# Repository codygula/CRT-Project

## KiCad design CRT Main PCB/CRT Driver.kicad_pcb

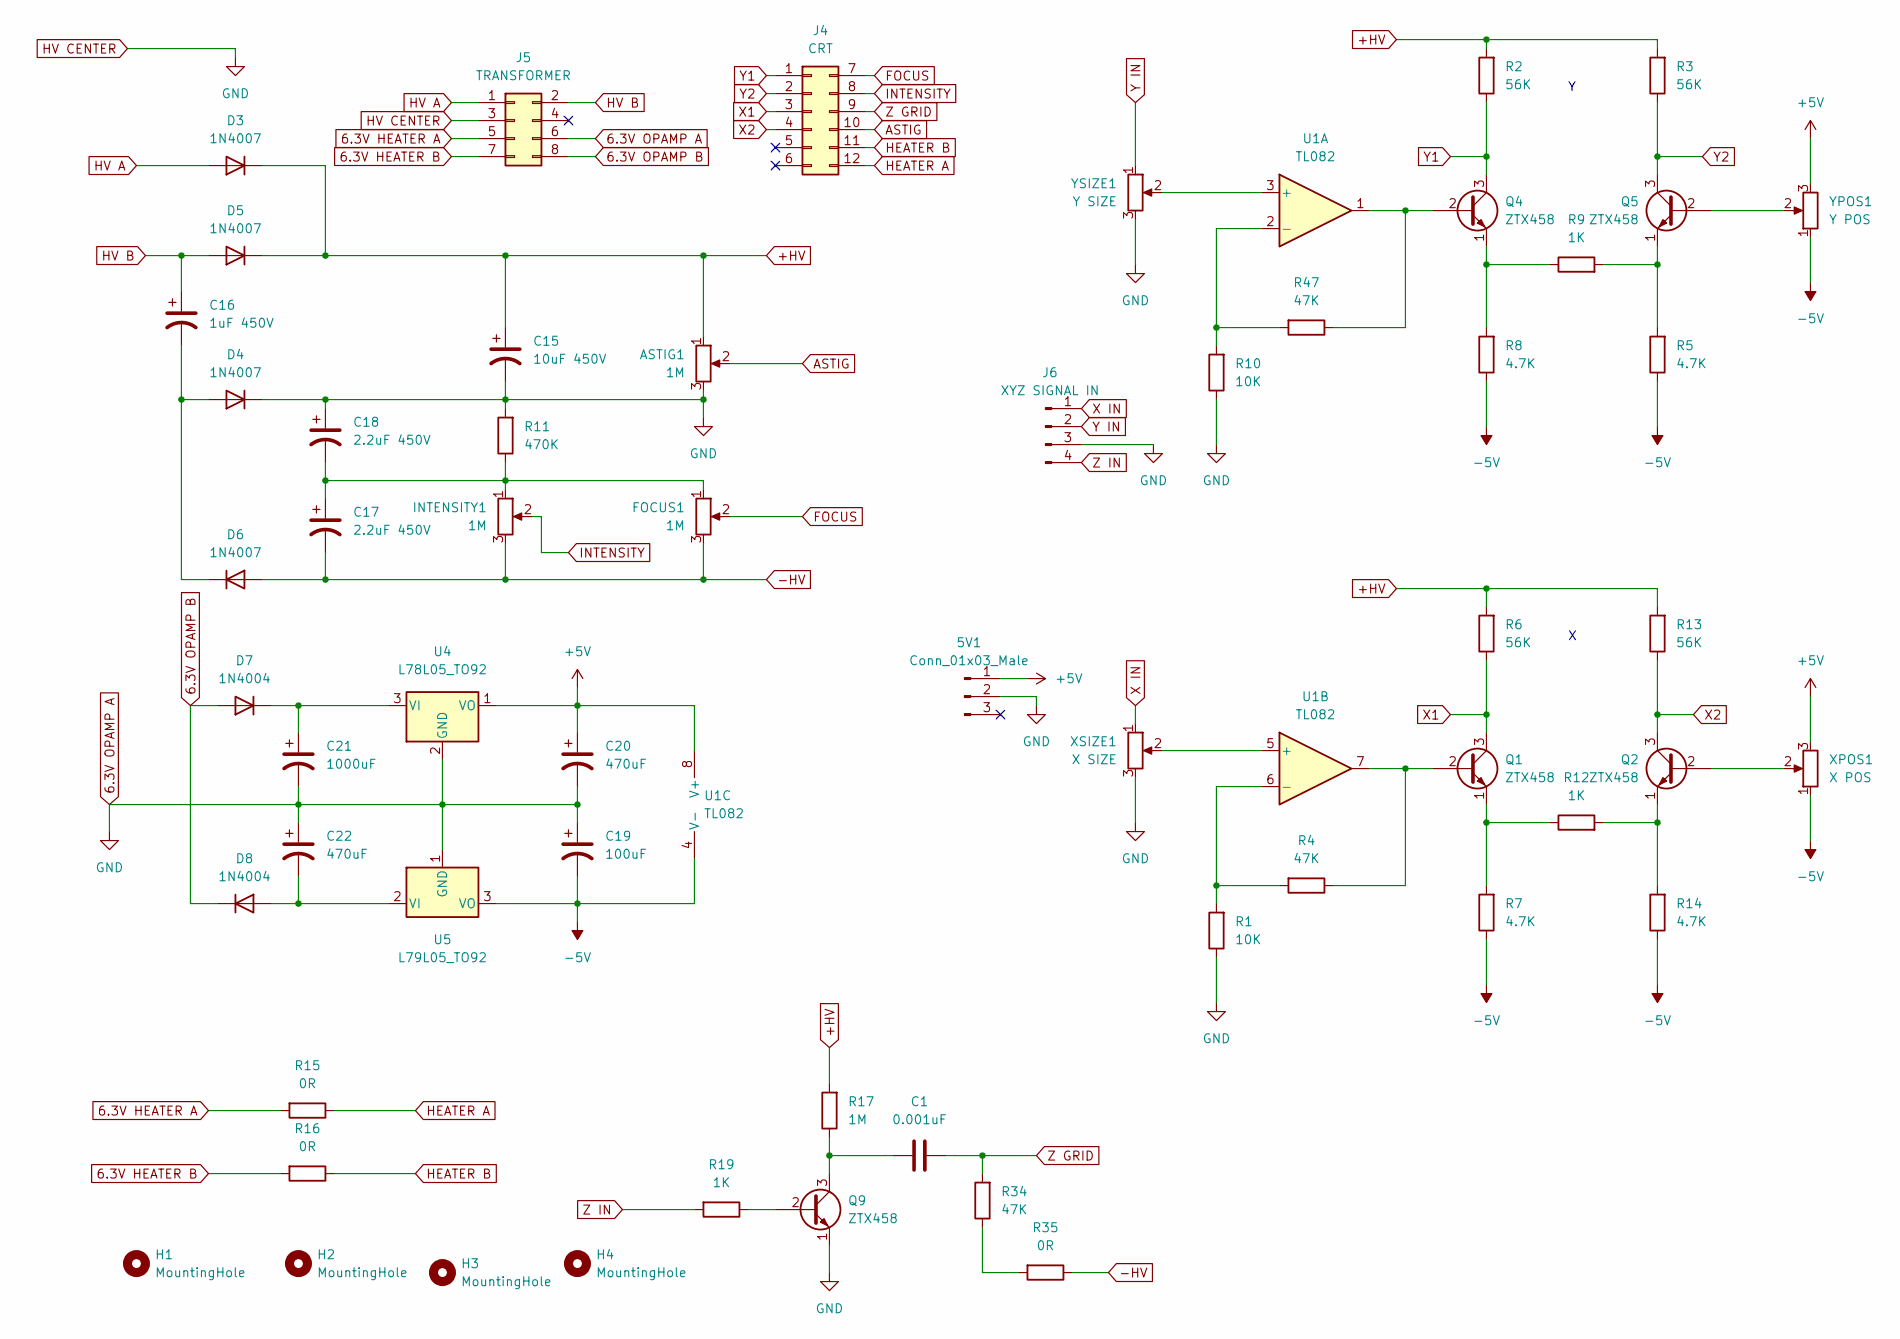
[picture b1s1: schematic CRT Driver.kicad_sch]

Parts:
5V1: Conn_01x03_Male; PinHeader_1x03_P2.54mm_Vertical
ASTIG1: 1M; Trimmer
C1: 0.001uF; C_Disc_D7.5mm_W5.0mm_P5.00mm
C15: 10uF 450V; CP_Radial_D10.0mm_P5.00mm
C16: 1uF 450V; CP_Radial_D7.5mm_P2.50mm
C17, C18: 2.2uF 450V; CP_Radial_D10.0mm_P5.00mm
C19: 100uF; CP_Radial_D5.0mm_P2.50mm
C20, C22: 470uF; CP_Radial_D8.0mm_P3.80mm
C21: 1000uF; CP_Radial_D8.0mm_P5.00mm
D3, D4, D5, D6: 1N4007; D_DO-41_SOD81_P10.16mm_Horizontal
D7, D8: 1N4004; D_DO-41_SOD81_P10.16mm_Horizontal
FOCUS1: 1M; Trimmer
H1, H2, H3, H4: MountingHole; MountingHole_2.7mm_Pad
INTENSITY1: 1M; Trimmer
J4: CRT; PinHeader_2x06_P2.54mm_Vertical
J5: TRANSFORMER; PinHeader_2x04_P2.54mm_Vertical
J6: XYZ SIGNAL IN; PinHeader_1x04_P2.54mm_Vertical
Q1, Q2, Q4, Q5, Q9: ZTX458; TO-92_Inline_Wide
R1, R10: 10K; R_Axial_DIN0207_L6.3mm_D2.5mm_P10.16mm_Horizontal
R2, R3, R6, R13: 56K; R_Axial_DIN0207_L6.3mm_D2.5mm_P10.16mm_Horizontal
R4, R34, R47: 47K; R_Axial_DIN0207_L6.3mm_D2.5mm_P10.16mm_Horizontal
R5, R7, R8, R14: 4.7K; R_Axial_DIN0207_L6.3mm_D2.5mm_P10.16mm_Horizontal
R9, R12, R19: 1K; R_Axial_DIN0207_L6.3mm_D2.5mm_P10.16mm_Horizontal
R11: 470K; R_Axial_DIN0207_L6.3mm_D2.5mm_P10.16mm_Horizontal
R15, R16, R35: 0R; R_Axial_DIN0207_L6.3mm_D2.5mm_P10.16mm_Horizontal
R17: 1M; R_Axial_DIN0207_L6.3mm_D2.5mm_P10.16mm_Horizontal
U1: TL082; DIP-8_W7.62mm
U4: L78L05_TO92; TO-92_Inline_Wide
U5: L79L05_TO92; TO-92_Inline_Wide
XPOS1: X POS; Trimmer
XSIZE1: X SIZE; Trimmer
YPOS1: Y POS; Trimmer
YSIZE1: Y SIZE; Trimmer

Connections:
6.3V HEATER A: J5.5, R15.2
6.3V HEATER B: J5.7, R16.2
6.3V OPAMP A: 5V1.2, ASTIG1.3, C15.2, C18.1, C19.1, C20.2, C21.2, C22.1, D4.1 (K), J5.3, J5.6, J6.3, Q9.1 (E), R1.1, R10.1, R11.2, U4.2 (GND), U5.1 (GND), XSIZE1.3, YSIZE1.3
6.3V OPAMP B: D7.2 (A), D8.1 (K), J5.8
+5V: 5V1.1, C20.1, U1.8 (V+), U4.1 (VO), XPOS1.3, YPOS1.3
+HV: ASTIG1.1, C15.1, D3.1 (K), D5.1 (K), R2.2, R3.2, R6.2, R13.2, R17.2
-5V: C19.2, R5.1, R7.1, R8.1, R14.1, U1.4 (V-), U5.3 (VO), XPOS1.1, YPOS1.1
-HV: C17.2, D6.2 (A), FOCUS1.3, INTENSITY1.3, R35.1
ASTIG: ASTIG1.2, J4.10
FOCUS: FOCUS1.2, J4.7
HEATER A: J4.12, R15.1
HEATER B: J4.11, R16.1
HV A: D3.2 (A), J5.1
HV B: C16.1, D5.2 (A), J5.2
INTENSITY: INTENSITY1.2, J4.8
unnamed: C1.1, Q9.3 (C), R17.1
unnamed: C16.2, D4.2 (A), D6.1 (K)
unnamed: C17.1, C18.2, FOCUS1.1, INTENSITY1.1, R11.1
unnamed: C21.1, D7.1 (K), U4.3 (VI)
unnamed: C22.2, D8.2 (A), U5.2 (VI)
unnamed: Q1.1 (E), R7.2, R12.1
unnamed: Q1.2 (B), R4.1, U1.7
unnamed: Q2.1 (E), R12.2, R14.2
unnamed: Q2.2 (B), XPOS1.2
unnamed: Q4.1 (E), R8.2, R9.1
unnamed: Q4.2 (B), R47.1, U1.1
unnamed: Q5.1 (E), R5.2, R9.2
unnamed: Q5.2 (B), YPOS1.2
unnamed: Q9.2 (B), R19.1
unnamed: R1.2, R4.2, U1.6 (-)
unnamed: R10.2, R47.2, U1.2 (-)
unnamed: R34.1, R35.2
unnamed: U1.3 (+), YSIZE1.2
unnamed: U1.5 (+), XSIZE1.2
X1: J4.3, Q1.3 (C), R6.1
X2: J4.4, Q2.3 (C), R13.1
X IN: J6.1, XSIZE1.1
Y1: J4.1, Q4.3 (C), R2.1
Y2: J4.2, Q5.3 (C), R3.1
Y IN: J6.2, YSIZE1.1
Z GRID: C1.2, J4.9, R34.2
Z IN: J6.4, R19.2

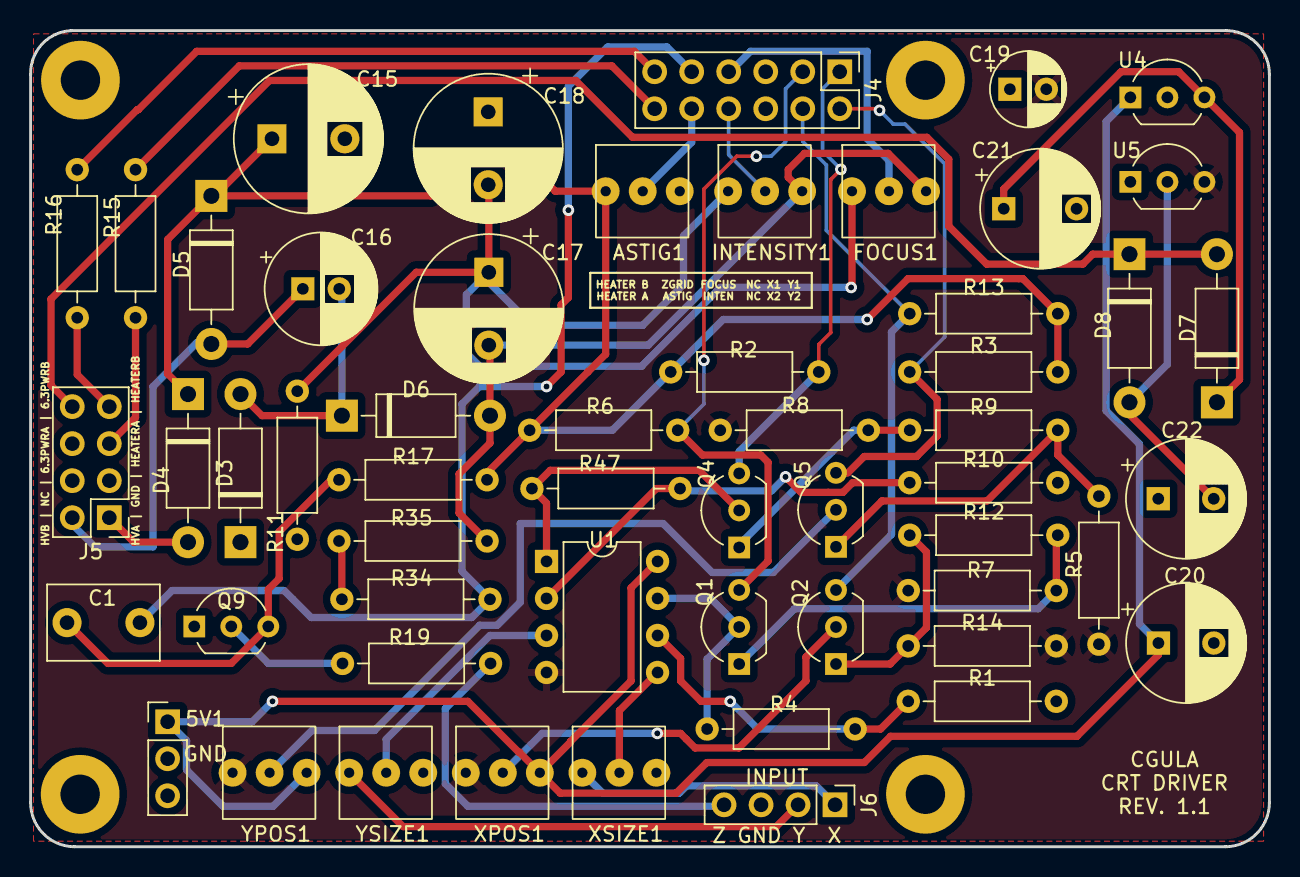
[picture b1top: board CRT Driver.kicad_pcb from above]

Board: 2 copper layers, 85.0 x 56.0 mm, 59 parts (0 on the bottom side), 42 nets.

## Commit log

2024-05-12 PCB Update
2024-05-15 PCB changes
2024-05-15 partly working test code
2024-05-17 added more useless comments
2024-05-18 fixed errors
2024-05-24 still not working
2024-05-25 ChatGPT Code
2024-05-26 still horrible
2024-06-13 Create ExamplePythonMenu.py
    Python menu code to translate into C++/Arduino code
